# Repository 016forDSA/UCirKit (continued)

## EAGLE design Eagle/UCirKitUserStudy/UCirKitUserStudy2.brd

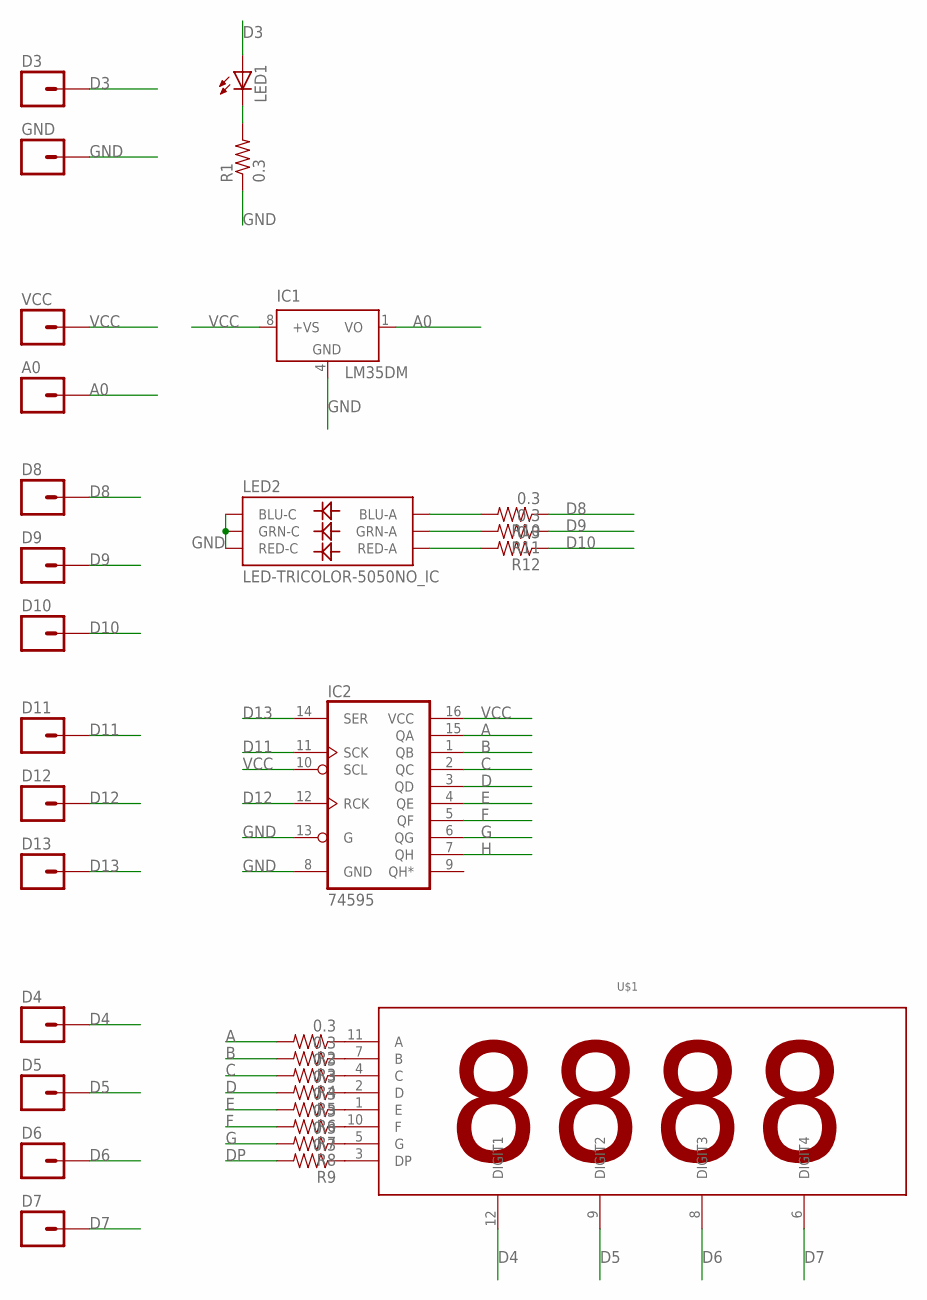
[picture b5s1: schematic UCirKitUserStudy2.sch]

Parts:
A0: M01PTH; 1X01
D3, D4, D5, D6, D7, D8, D9, D10, D11, D12, D13: M01PTH; 1X01
GND: M01PTH; 1X01
IC1: LM35DM; SO08
IC2: 74595; TSSOP16
LED1: LEDCHIPLED_0805; CHIPLED_0805
LED2: LED-TRICOLOR-5050NO_IC; LED-TRICOLOR-5050
R1, R2, R3, R4, R5, R6, R7, R8, R9, R10, R11, R12: 0.3; 0805
U$1: 4DIGIT_SEVEN_SEGMENT4DIGIT_SEVEN_SEGMENT_FAR_PINS; 4DIGIT_SEVEN_SEGMENT_FAR_PINS
VCC: M01PTH; 1X01

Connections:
A: IC2.15 (QA), R2.2
A0: A0.1, IC1.1 (VO)
B: IC2.1 (QB), R3.2
C: IC2.2 (QC), R4.2
D: IC2.3 (QD), R5.2
D3: D3.1, LED1.A
D4: D4.1, U$1.12 (DIGIT1)
D5: D5.1, U$1.9 (DIGIT2)
D6: D6.1, U$1.8 (DIGIT3)
D7: D7.1, U$1.6 (DIGIT4)
D8: D8.1, R10.1
D9: D9.1, R11.1
D10: D10.1, R12.1
D11: D11.1, IC2.11 (SCK)
D12: D12.1, IC2.12 (RCK)
D13: D13.1, IC2.14 (SER)
DP: R9.2
E: IC2.4 (QE), R6.2
F: IC2.5 (QF), R7.2
G: IC2.6 (QG), R8.2
GND: GND.1, IC1.4 (GND), IC2.8 (GND), IC2.13 (G), LED2.4 (BLU-C), LED2.5 (RED-C), LED2.6 (GRN-C), R1.1
H: IC2.7 (QH)
unnamed: LED1.C, R1.2
unnamed: R2.1, U$1.11 (A)
unnamed: R3.1, U$1.7 (B)
unnamed: R4.1, U$1.4 (C)
unnamed: R5.1, U$1.2 (D)
unnamed: R6.1, U$1.1 (E)
unnamed: R7.1, U$1.10 (F)
unnamed: R8.1, U$1.5 (G)
unnamed: R9.1, U$1.3 (DP)
unnamed: LED2.3 (BLU-A), R10.2
unnamed: LED2.1 (GRN-A), R11.2
unnamed: LED2.2 (RED-A), R12.2
VCC: IC1.8 (+VS), IC2.10 (SCL), IC2.16 (VCC), VCC.1

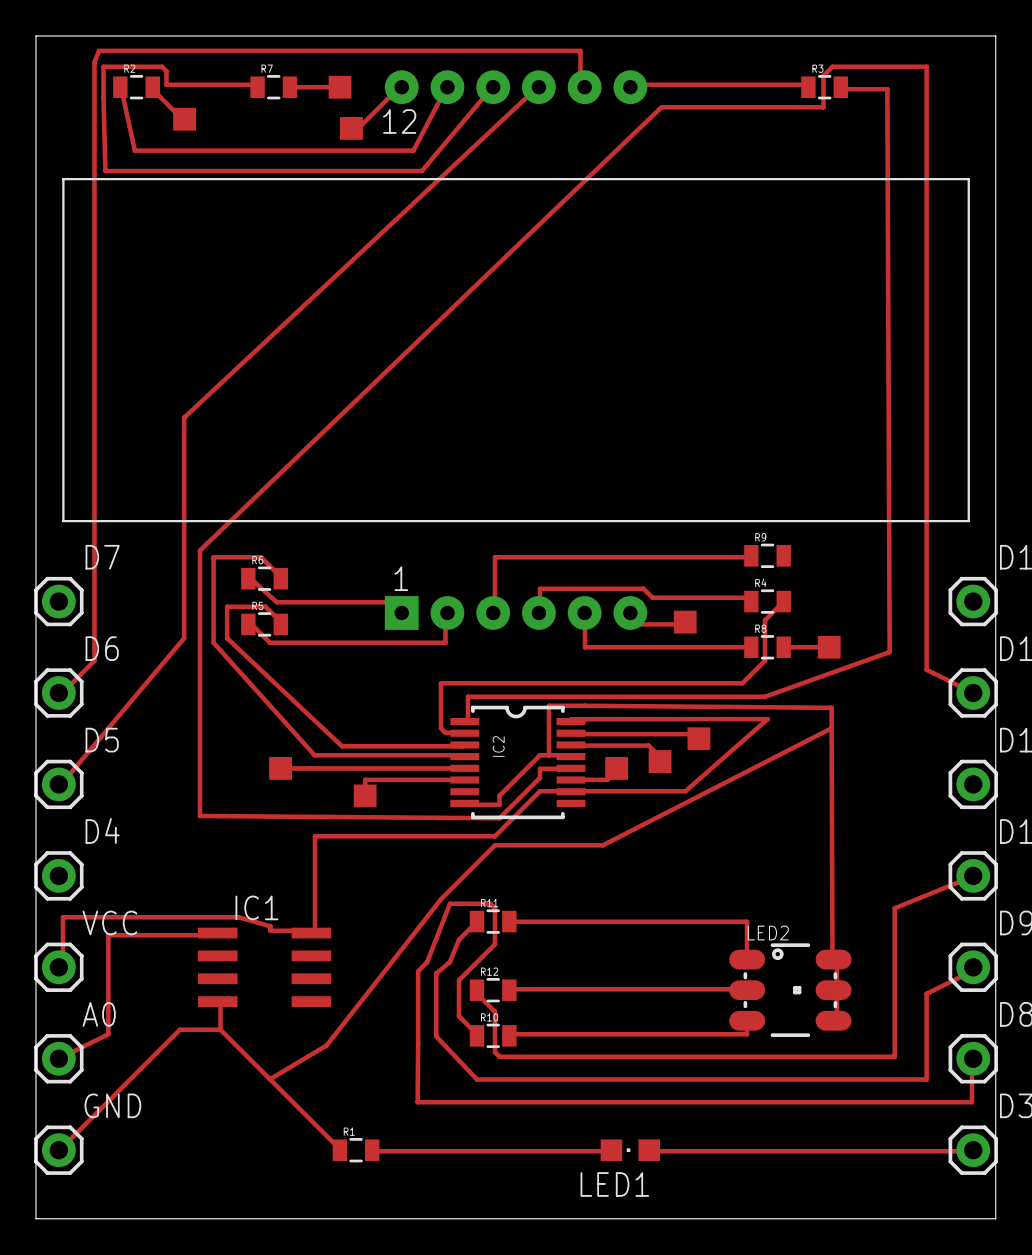
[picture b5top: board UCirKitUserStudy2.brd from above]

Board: 2 copper layers, 53.3 x 65.7 mm, 31 parts (0 on the bottom side), 33 nets.

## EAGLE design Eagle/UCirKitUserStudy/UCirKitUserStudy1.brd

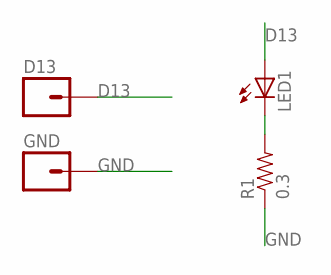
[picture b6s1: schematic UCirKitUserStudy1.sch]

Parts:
D13: M01PTH; 1X01
GND: M01PTH; 1X01
LED1: LEDCHIPLED_0805; CHIPLED_0805
R1: 0.3; 0805

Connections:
D13: D13.1, LED1.A
GND: GND.1, R1.1
unnamed: LED1.C, R1.2

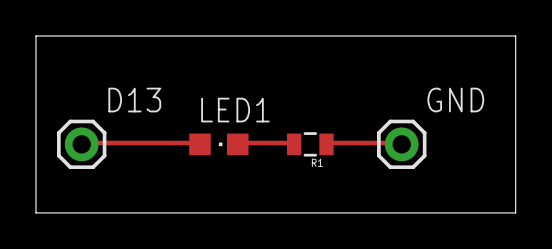
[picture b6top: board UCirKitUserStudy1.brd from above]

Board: 2 copper layers, 26.6 x 9.8 mm, 4 parts (0 on the bottom side), 3 nets.

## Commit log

2015-07-23 Create Eagle
2015-07-25 權我好廢你最強了快教我script
2015-07-27 可以PCB了
2015-07-28 example ulp scripts
2015-07-31 now with UL_PinTest.ulp to get all information we need
2015-07-31 RenameNet.ulp, UL_ContactRefTest.ulp, UL_PinTest.ulp uploaded
2015-08-01 RenameWireByPin.ulp uploaded
2015-08-01 create more directories
2015-08-02 fzP.py uploaded. Can get wire information from fritzing directly
2015-08-02 RenameMinDis.ulp in Debug mode ( last line + exit(cmd) to execute
2015-08-02 RenameMinDis.ulp done except for clicking OK
2015-08-02 UCirKitCompleteScript now creates female headers on schematic
2015-08-03 Final Version of RenameMinDis.ulp
2015-08-04 breadboard version
2015-08-05 RenameBreadBoardLike.ulp
2015-08-06 Latest Version of RenameMinDis.ulp
2015-08-06 UCirKit 30x10 with Spacing added!
2015-08-06 GroupSelectConnectWire.ulp is complete!
2015-08-06 single pin
2015-08-07 bug fix on GroupSelectConnectWire.ulp by adding time() to naming
2015-08-07 RenameAllNetToClean.ulp script uploaded
2015-08-08 Comment out GroupSelectConnectWire.ulp debug code segments
2015-08-08 Routed Files
2015-08-11 almost done version board
2015-08-12 UCirKitBreadboardWithEverything.ulp
2015-08-12 Update Sparkfun-Connectors Library
2015-08-12 UCirKitBreadboardTop completes routing!
2015-08-12 100% Bottom PCB
2015-08-13 customized RenameBreadBoardLike.ulp
2015-08-13 Bottom2.brd and Bottom.zip ( Gerber file )
2015-08-13 UCirKitBreadboardTop Gerber files
2015-08-13 Correct UCirKitBreadboardTop Gerber files
2015-08-13 UCirKitBreadboardTop new gerber again
2015-08-13 UCirKitBreadboardBottom updated with wider width of central contact points
2015-08-16 Let's Debugggggg~
2015-08-16 new scripts for arranging the elements on board
2015-08-18 A little error UCirKitBreadboardWithEverthing2 is Bottom part
2015-08-18 UCirKitEverything2Top is OK for Routing, UCirKitEverything2 is not OK. Look for UCirKitEverything2 for Bottom part
2015-08-21 Version UCirKitBreadboardWithEverything-08201626 complete. New GroupSelectConnectWire_v2 script to get truly min distance
2015-08-21 new SparkFun-Connectors library
2015-08-22 New code that auto arranges all parts making symmetry about the central vertical axis
2015-08-23 New version 0823 complete routing with symmetrical part positions and M3 holes
2015-08-23 New design version 08231908 along with new code. This version moves outer pads closer to edges!
2015-08-23 Version 08231908 gerber file uploaded. Row number added to tPlace layer
2015-08-24 Version 0824 uploaded. Bottom layer has both top side and bottom side inner pads.
2015-08-30 user study eagle files
2015-09-03 code for generating uCirKit Board
2015-09-04 UCirKitUserStudy5 has SMD version of resistor, LED, and RGBLED. UCirKitUserStudy4 has oval shape for jumpers.
2015-09-05 UCirKitUserStudy4-2 and UCirKitUserStudy5-2 introduces 90 degree male headers for jumper wires
2015-09-06 UCirKitUserStudy5-3 created having intervals between groups of headers
2015-09-27 minor changes
2015-10-06 From Fritzing to Eagle Print ulp
2015-10-06 solve conflict
2015-10-07 PCP Print Version
2016-02-21 added codes with contact plates for paper on the top layer
2016-02-21 change the contact plate position arrangement from part 3 to 4b
2016-02-21 fix breadboard arrangement error with an extra spacing of 2.54 mm in the middle aisle
2016-02-21 platePadForPaper now uses 7.5 x 0.8 mm
2016-02-21 now can have vertical and horizontal symmetric arrangements
2016-02-21 now can properly create contact plates for paper with symmetry
2016-02-22 change variable name for horizontal and vertical contact plates for paper
2016-02-23 AddFemaleHeaderArray now prevents parts going out of schematic range
2016-02-23 Now adds contact plates to schematics
2016-02-23 arranges contact plates for holes
2016-02-23 fix contact plates global variable computation
2016-02-24 arrangement script is split into multiple functions
2016-02-24 change plate parts for paper to the same as that of hole parts
2016-02-26 added some "if else" to let rotation and mirror only effective to the required parts
2016-02-26 fix bug of plate pad arrangements
2016-02-26 added fiducial marks
2016-03-03 CircuitStack breadboard version
2016-03-04 fix spacing between plate pads for paper
2016-03-04 added more spring contacts for shorted column pins
2016-03-04 New script: connect all the selected components
2016-03-05 64 row breadboard parameter
2016-03-08 text numbering completes
2016-03-08 now able to use square span to connect parts
2016-03-08 change inner shorted pin layout
2016-03-08 added text numbering to part 5
